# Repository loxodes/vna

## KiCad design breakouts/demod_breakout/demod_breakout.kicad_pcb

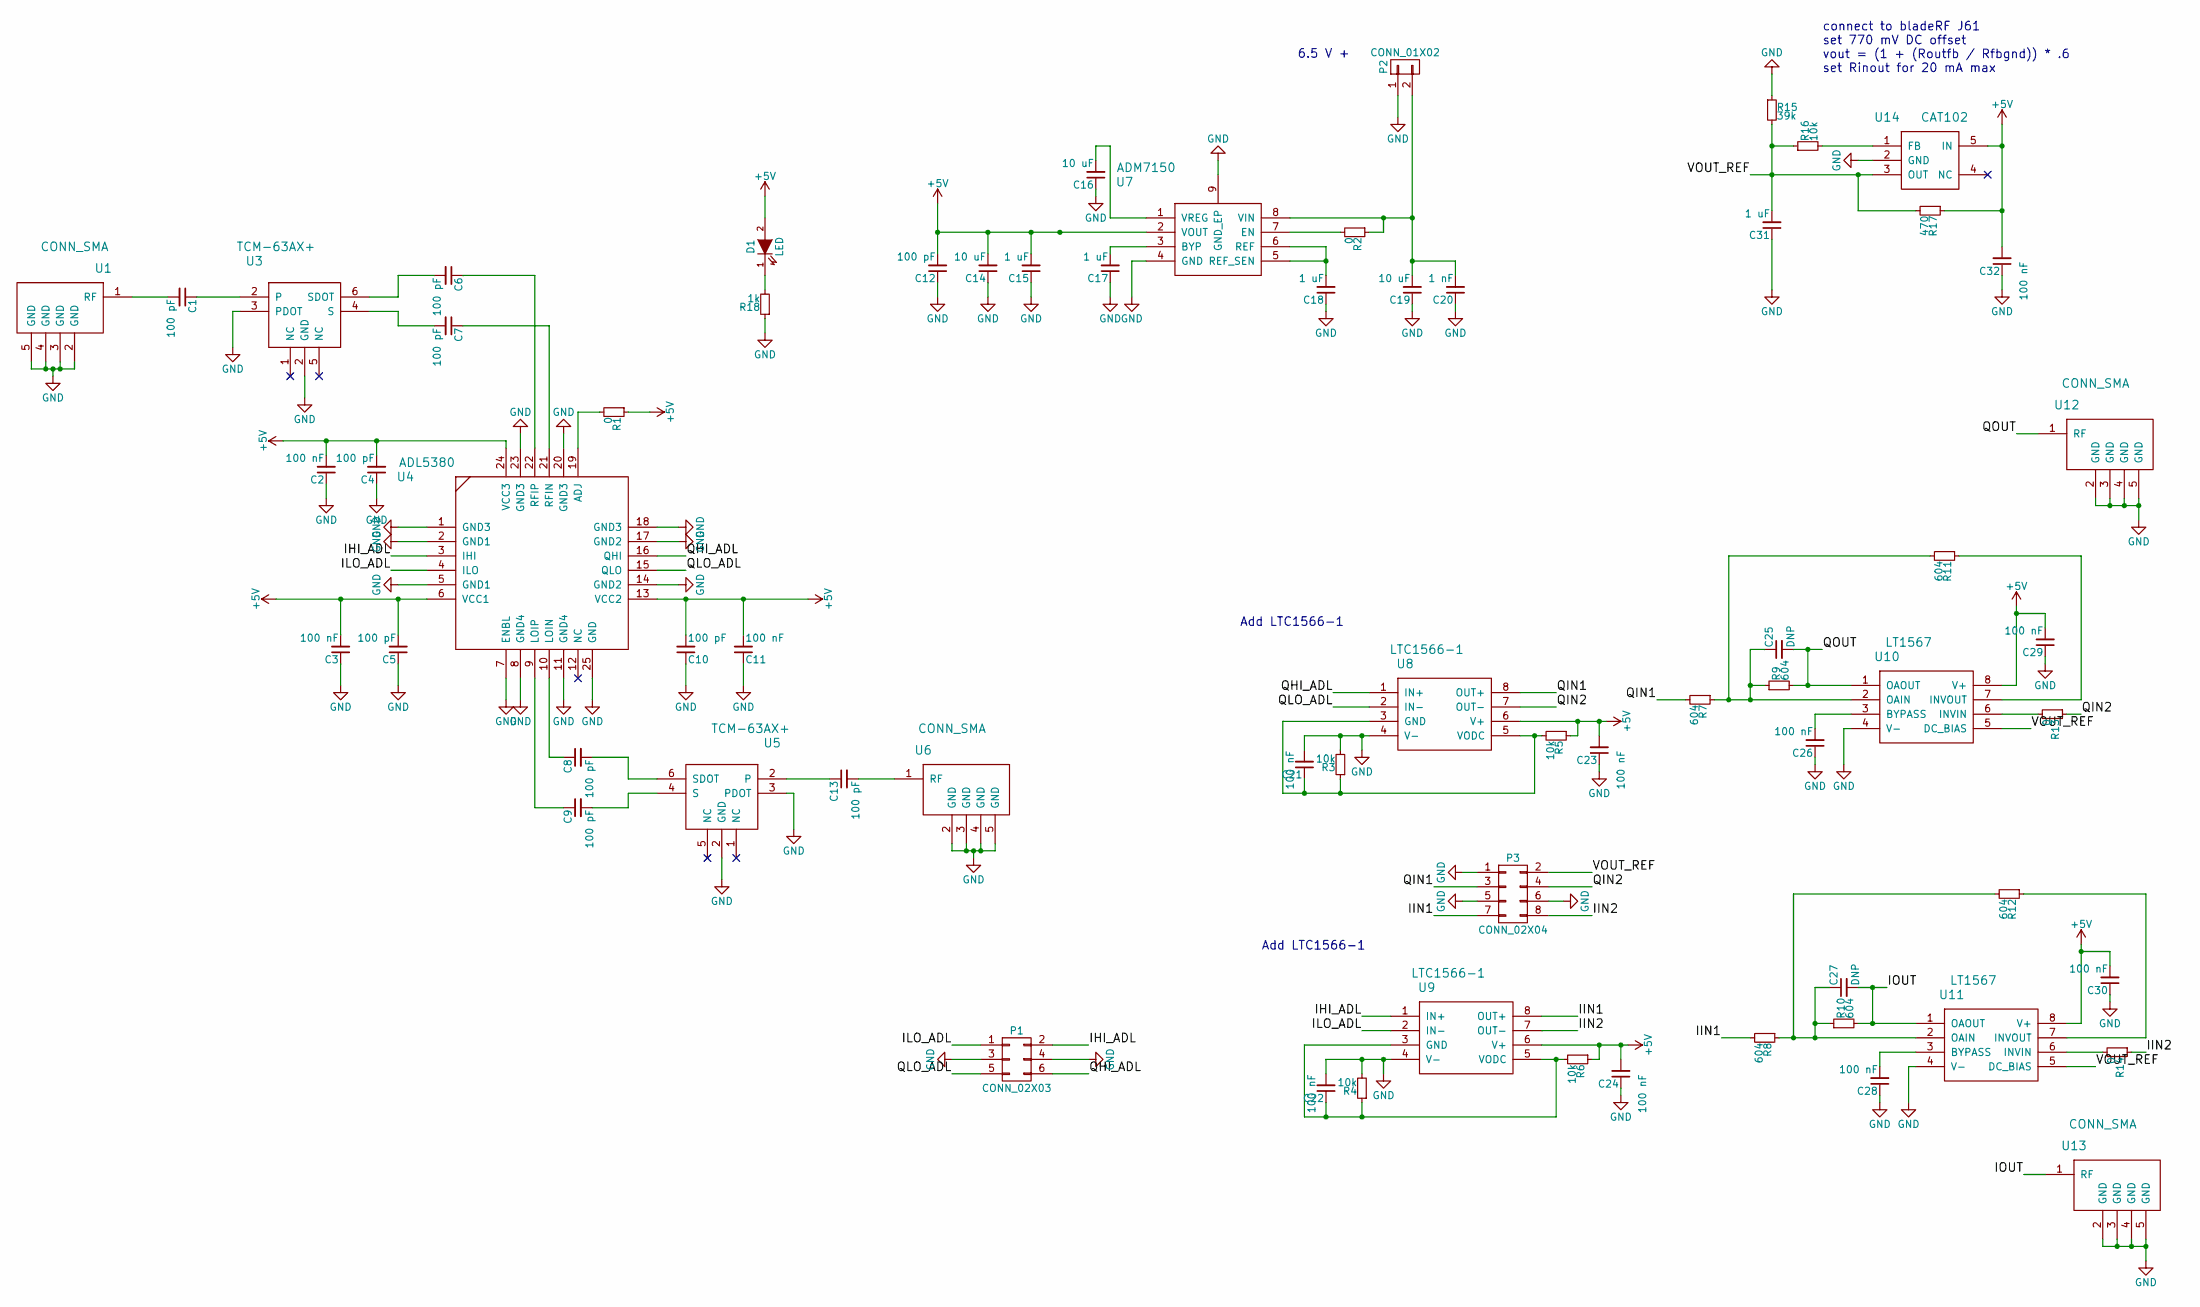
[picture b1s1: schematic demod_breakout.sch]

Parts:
C1, C4, C5, C6, C7, C8, C9, C10, C12, C13: 100 pF; C_0402
C2, C3, C11, C21, C22, C23, C24, C26, C28, C29, C30, C32: 100 nF; C_0402
C14, C16, C19: 10 uF; C_0805
C15, C17, C18, C31: 1 uF; C_0402
C20: 1 nF; C_0402
C25, C27: DNP; C_0402
D1: LED; LED_0603
P1: CONN_02X03; Pin_Header_Straight_2x03
P2: CONN_01X02; Pin_Header_Straight_1x02
P3: CONN_02X04; Pin_Header_Straight_2x04
R1, R2, R13, R14: 0; R_0402
R3, R4, R5, R6, R16: 10k; R_0402
R7, R8, R9, R10, R11, R12: 604; R_0402
R15: 39k; R_0402
R17: 470; R_0402
R18: 1k; R_0402
U1, U6, U12, U13: CONN_SMA; 732512200_SMA
U3, U5: TCM-63AX+; TCM1-63AX+
U4: ADL5380; QFN-24-1EP_4x4mm_Pitch0.5mm
U7: ADM7150; DFN-8-1EP_3x3mm_Pitch0.5mm
U8, U9: LTC1566-1; SOIC-8_3.9x4.9mm_Pitch1.27mm
U10, U11: LT1567; MSOP-8_3x3mm_Pitch0.65mm
U14: CAT102; SOT-23-5

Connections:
+5V: C2.2, C3.2, C4.2, C5.2, C10.2, C11.2, C12.2, C14.2, C15.2, C23.2, C24.2, C29.2, C30.2, C32.2, D1.2 (A), R1.1, R5.1, R6.1, R17.1, U4.6 (VCC1), U4.13 (VCC2), U4.24 (VCC3), U7.2 (VOUT), U8.6 (V+), U9.6 (V+), U10.8 (V+), U11.8 (V+), U14.5 (IN)
/IHI_ADL: P1.2, U4.3 (IHI), U9.1 (IN+)
/IIN1: P3.7, R8.2, U9.8 (OUT+)
/IIN2: P3.8, R14.1, U9.7 (OUT-)
/ILO_ADL: P1.1, U4.4 (ILO), U9.2 (IN-)
/IOUT: C27.2, R10.2, U11.1 (OAOUT), U13.1 (RF)
/QHI_ADL: P1.6, U4.16 (QHI), U8.1 (IN+)
/QIN1: P3.3, R7.2, U8.8 (OUT+)
/QIN2: P3.4, R13.1, U8.7 (OUT-)
/QLO_ADL: P1.5, U4.15 (QLO), U8.2 (IN-)
/QOUT: C25.2, R9.2, U10.1 (OAOUT), U12.1 (RF)
/VOUT_REF: C31.2, P3.2, R15.2, R16.1, R17.2, U10.5 (DC_BIAS), U11.5 (DC_BIAS), U14.3 (OUT)
unnamed: C1.2, U1.1 (RF)
unnamed: C6.1, U4.22 (RFIP)
unnamed: C6.2, U3.6 (SDOT)
unnamed: C7.1, U4.21 (RFIN)
unnamed: C7.2, U3.4 (S)
unnamed: C8.1, U4.10 (LOIN)
unnamed: C8.2, U5.6 (SDOT)
unnamed: C9.1, U4.9 (LOIP)
unnamed: C9.2, U5.4 (S)
unnamed: C13.2, U6.1 (RF)
unnamed: C16.2, U7.1 (VREG)
unnamed: C17.2, U7.3 (BYP)
unnamed: C18.2, U7.5 (REF_SEN), U7.6 (REF)
unnamed: C19.2, C20.2, P2.2, R2.1, U7.8 (VIN)
unnamed: C21.1, R3.1, R5.2, U8.3 (GND), U8.5 (VODC)
unnamed: C22.1, R4.1, R6.2, U9.3 (GND), U9.5 (VODC)
unnamed: C25.1, R7.1, R9.1, R11.2, U10.2 (OAIN)
unnamed: C26.2, U10.3 (BYPASS)
unnamed: C27.1, R8.1, R10.1, R12.2, U11.2 (OAIN)
unnamed: C28.2, U11.3 (BYPASS)
unnamed: D1.1 (K), R18.2
unnamed: R1.2, U4.19 (ADJ)
unnamed: R2.2, U7.7 (EN)
unnamed: R11.1, U10.7 (INVOUT)
unnamed: R12.1, U11.7 (INVOUT)
unnamed: R13.2, U10.6 (INVIN)
unnamed: R14.2, U11.6 (INVIN)
unnamed: R16.2, U14.1 (FB)

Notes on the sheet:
6.5 V +
connect to bladeRF J61 set 770 mV DC offset vout = (1 + (Routfb / Rfbgnd)) * .6 set Rinout for 20 mA max
Add LTC1566-1

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
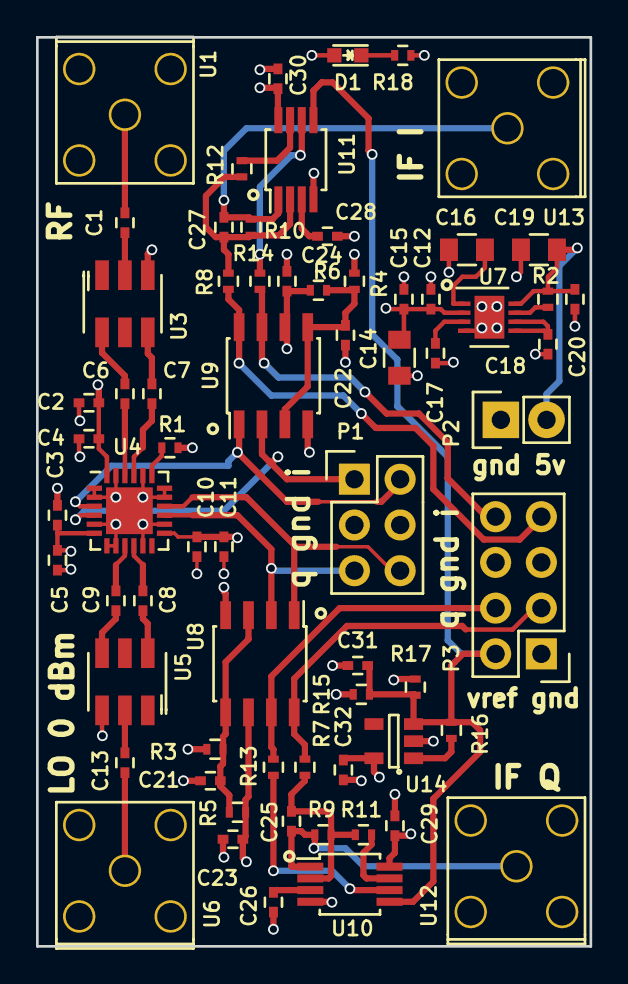
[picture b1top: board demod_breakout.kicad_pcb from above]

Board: 4 copper layers, 30.8 x 50.5 mm, 67 parts (0 on the bottom side), 43 nets.

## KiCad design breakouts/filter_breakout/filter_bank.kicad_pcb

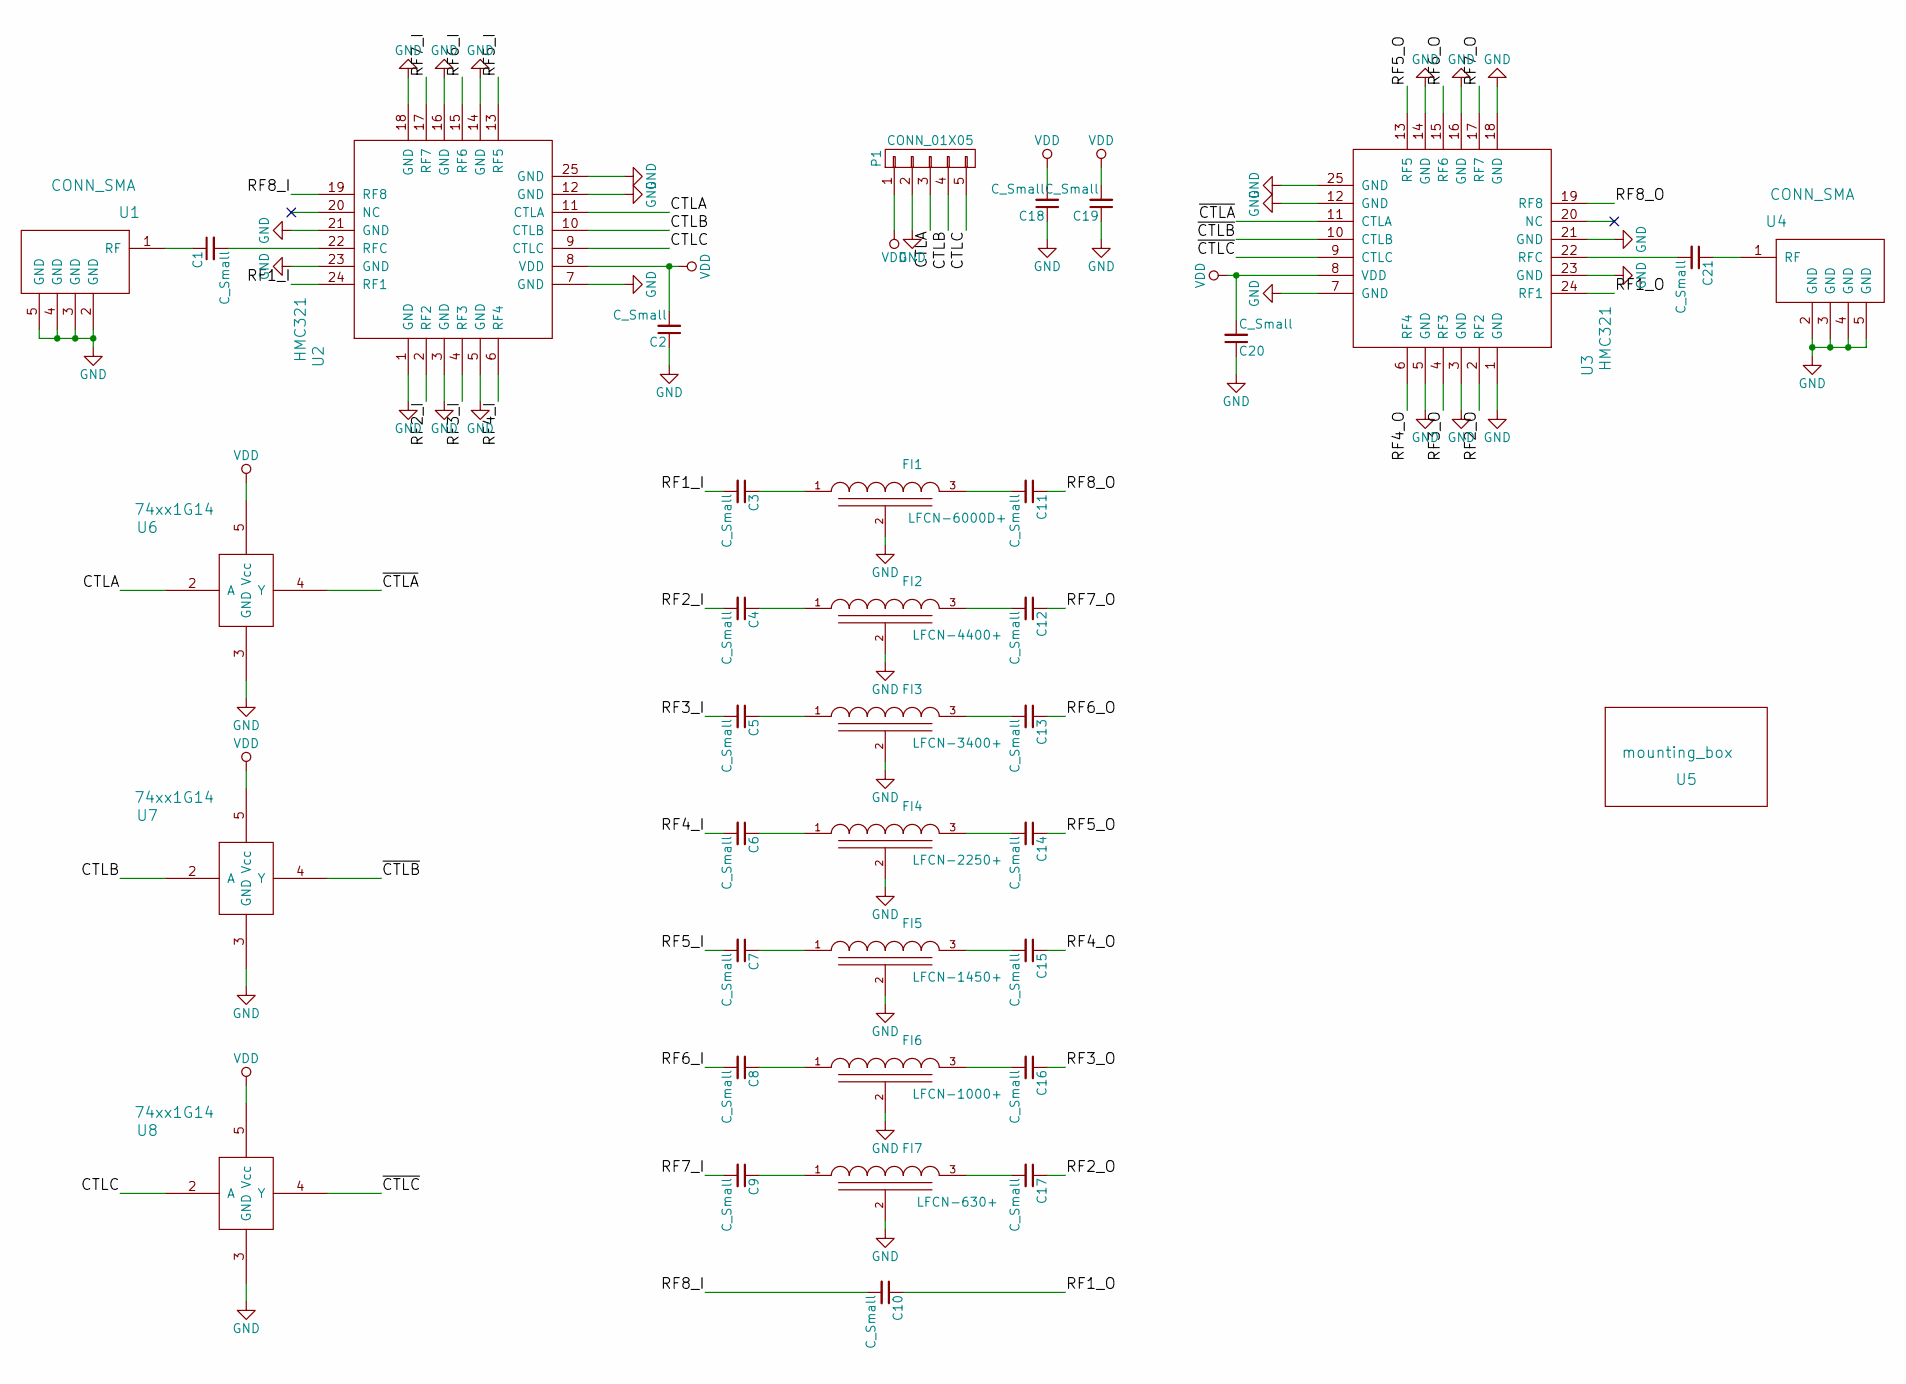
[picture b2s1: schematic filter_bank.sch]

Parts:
C1, C2, C3, C4, C5, C6, C7, C8, C9, C10, C11, C12, C13, C14, C15, C16, C17, C19, C20, C21: C_Small; C_0402
C18: C_Small; C_0805
FI1: LFCN-6000D+; FV1206
FI2: LFCN-4400+; FV1206
FI3: LFCN-3400+; FV1206
FI4: LFCN-2250+; FV1206
FI5: LFCN-1450+; FV1206
FI6: LFCN-1000+; FV1206
FI7: LFCN-630+; FV1206
P1: CONN_01X05; Pin_Header_Straight_1x05
U1, U4: CONN_SMA; 732511150_sma
U2, U3: HMC321; QFN-24-1EP_4x4mm_Pitch0.5mm
U5: mounting_box; POMONA_2400BOX
U6, U7, U8: 74xx1G14; SOT-23-5

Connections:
/CTLA: P1.3, U2.11 (CTLA), U6.2 (A)
/CTLB: P1.4, U2.10 (CTLB), U7.2 (A)
/CTLC: P1.5, U2.9 (CTLC), U8.2 (A)
/RF1_I: C3.2, U2.24 (RF1)
/RF1_O: C10.1, U3.24 (RF1)
/RF2_I: C4.2, U2.2 (RF2)
/RF2_O: C17.1, U3.2 (RF2)
/RF3_I: C5.2, U2.4 (RF3)
/RF3_O: C16.1, U3.4 (RF3)
/RF4_I: C6.2, U2.6 (RF4)
/RF4_O: C15.1, U3.6 (RF4)
/RF5_I: C7.2, U2.13 (RF5)
/RF5_O: C14.1, U3.13 (RF5)
/RF6_I: C8.2, U2.15 (RF6)
/RF6_O: C13.1, U3.15 (RF6)
/RF7_I: C9.2, U2.17 (RF7)
/RF7_O: C12.1, U3.17 (RF7)
/RF8_I: C10.2, U2.19 (RF8)
/RF8_O: C11.1, U3.19 (RF8)
/~CTLA: U3.11 (CTLA), U6.4 (Y)
/~CTLB: U3.10 (CTLB), U7.4 (Y)
/~CTLC: U3.9 (CTLC), U8.4 (Y)
GND: C2.1, C18.1, C19.1, C20.1, FI1.2 (GND), FI2.2 (GND), FI3.2 (GND), FI4.2 (GND), FI5.2 (GND), FI6.2 (GND), FI7.2 (GND), P1.2, U1.2 (GND), U1.3 (GND), U1.4 (GND), U1.5 (GND), U2.1 (GND), U2.3 (GND), U2.5 (GND), U2.7 (GND), U2.12 (GND), U2.14 (GND), U2.16 (GND), U2.18 (GND), U2.21 (GND), U2.23 (GND), U2.25 (GND), U3.1 (GND), U3.3 (GND), U3.5 (GND), U3.7 (GND), U3.12 (GND), U3.14 (GND), U3.16 (GND), U3.18 (GND), U3.21 (GND), U3.23 (GND), U3.25 (GND), U4.2 (GND), U4.3 (GND), U4.4 (GND), U4.5 (GND), U6.3 (GND), U7.3 (GND), U8.3 (GND)
unnamed: C1.1, U1.1 (RF)
unnamed: C1.2, U2.22 (RFC)
unnamed: C3.1, FI1.1 (VI)
unnamed: C4.1, FI2.1 (VI)
unnamed: C5.1, FI3.1 (VI)
unnamed: C6.1, FI4.1 (VI)
unnamed: C7.1, FI5.1 (VI)
unnamed: C8.1, FI6.1 (VI)
unnamed: C9.1, FI7.1 (VI)
unnamed: C11.2, FI1.3 (VO)
unnamed: C12.2, FI2.3 (VO)
unnamed: C13.2, FI3.3 (VO)
unnamed: C14.2, FI4.3 (VO)
unnamed: C15.2, FI5.3 (VO)
unnamed: C16.2, FI6.3 (VO)
unnamed: C17.2, FI7.3 (VO)
unnamed: C21.1, U4.1 (RF)
unnamed: C21.2, U3.22 (RFC)
VDD: C2.2, C18.2, C19.2, C20.2, P1.1, U2.8 (VDD), U3.8 (VDD), U6.5 (Vcc), U7.5 (Vcc), U8.5 (Vcc)

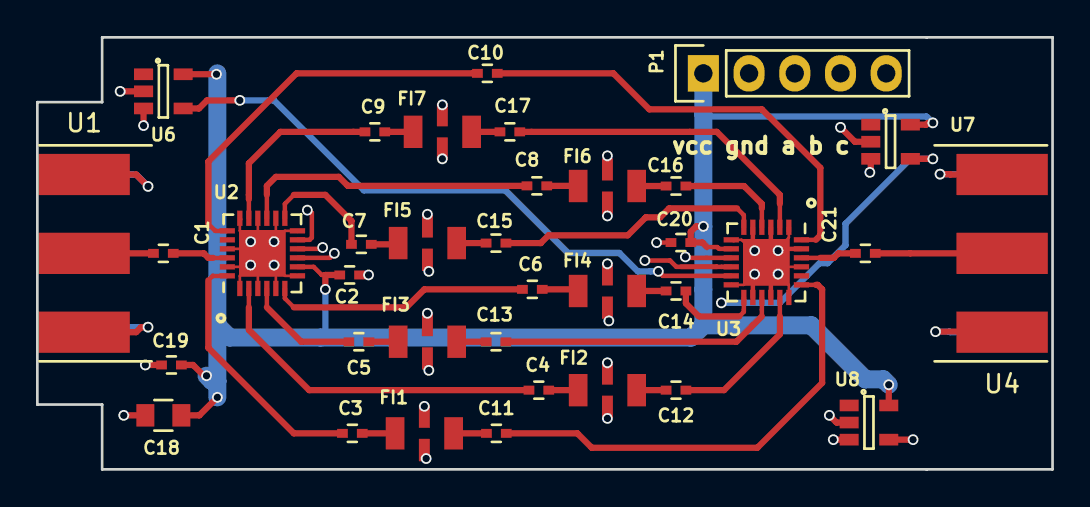
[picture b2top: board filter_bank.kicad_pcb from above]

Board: 4 copper layers, 56.4 x 24.0 mm, 36 parts (0 on the bottom side), 42 nets.

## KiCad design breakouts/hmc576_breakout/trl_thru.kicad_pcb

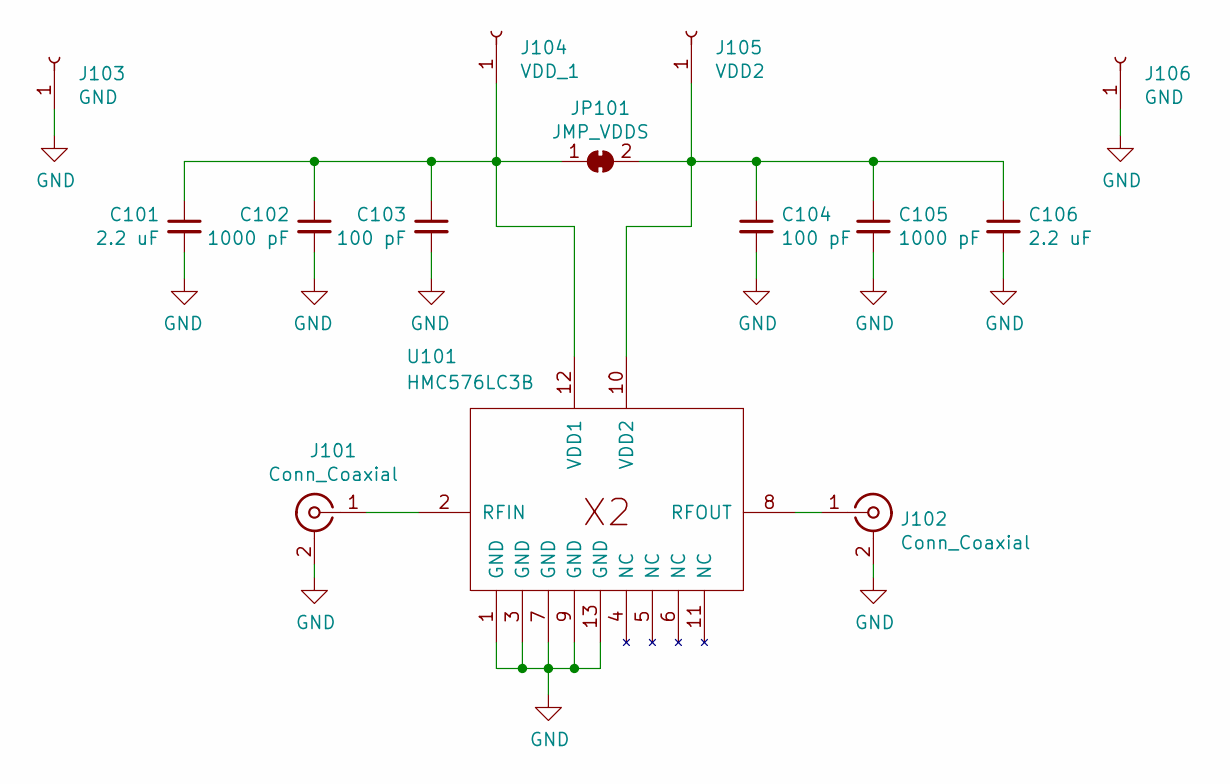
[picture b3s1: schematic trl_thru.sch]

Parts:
C101, C106: 2.2 uF; C_0805
C102, C105: 1000 pF; C_0402
C103, C104: 100 pF; C_0402
J101, J102: Conn_Coaxial; sw_edge_oshpark_4layer
J103, J106: GND; TURRET_MILLMAX_2101
J104: VDD_1; TURRET_MILLMAX_2101
J105: VDD2; TURRET_MILLMAX_2101
JP101: JMP_VDDS; R_0402
U101: HMC576LC3B; LC3B

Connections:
GND: C101.2, C102.2, C103.2, C104.2, C105.2, C106.2, J101.2 (Ext), J102.2 (Ext), J103.1, J106.1, U101.1 (GND), U101.3 (GND), U101.7 (GND), U101.9 (GND), U101.13 (GND)
unnamed: C101.1, C102.1, C103.1, J104.1, JP101.1 (A), U101.12 (VDD1)
unnamed: C104.1, C105.1, C106.1, J105.1, JP101.2 (B), U101.10 (VDD2)
unnamed: J101.1 (In), U101.2 (RFIN)
unnamed: J102.1 (In), U101.8 (RFOUT)

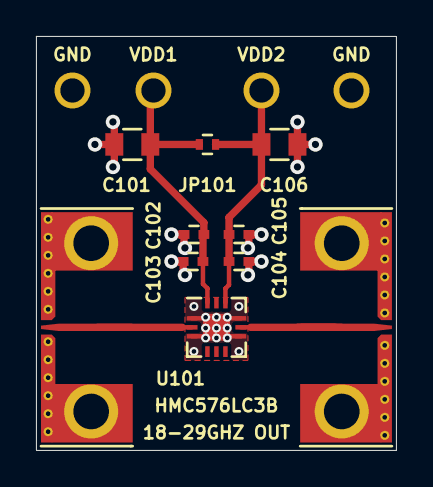
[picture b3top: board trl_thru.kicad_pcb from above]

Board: 4 copper layers, 20.0 x 23.0 mm, 14 parts (0 on the bottom side), 5 nets.

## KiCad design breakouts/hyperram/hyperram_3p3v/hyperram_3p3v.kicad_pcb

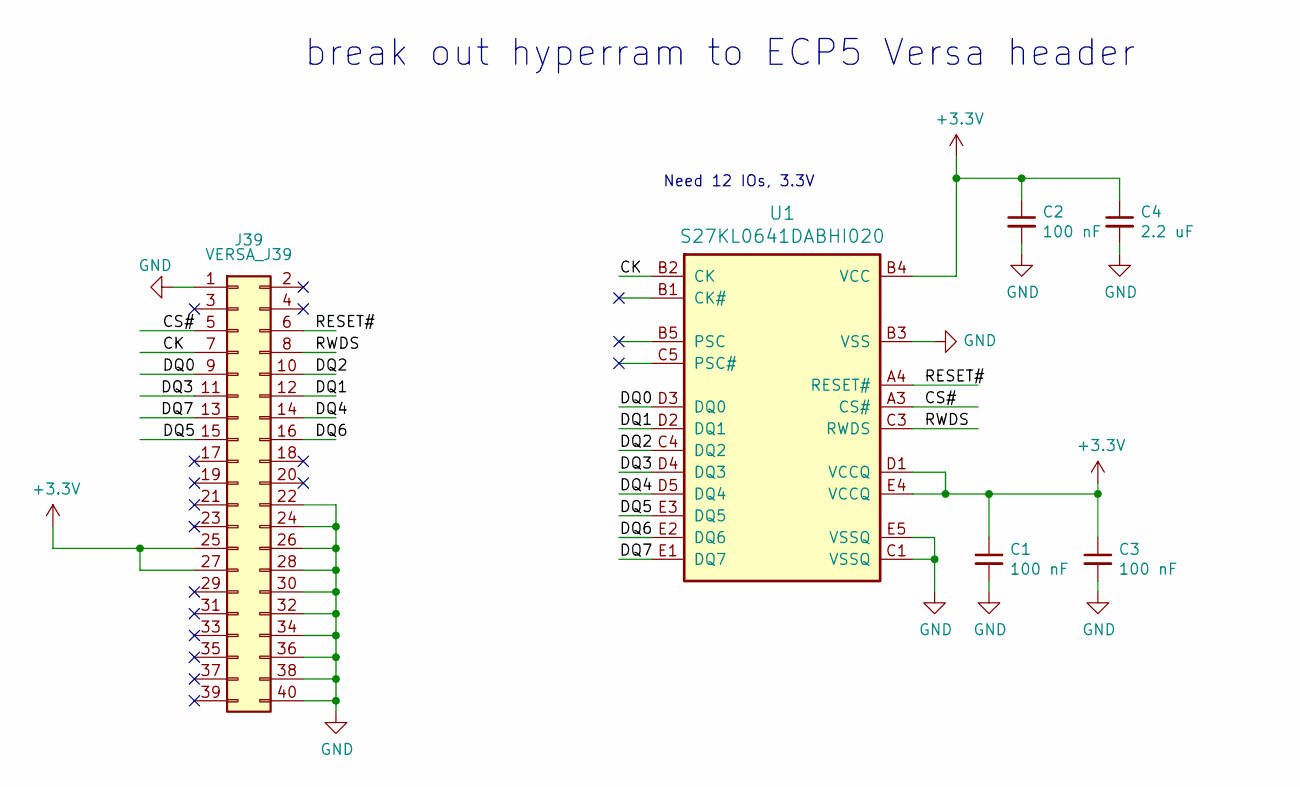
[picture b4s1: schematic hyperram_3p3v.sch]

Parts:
C1, C2, C3: 100 nF; C_0402_1005Metric
C4: 2.2 uF; C_0603_1608Metric
J39: VERSA_J39; PinSocket_2x20_P2.54mm_Vertical
U1: S27KL0641DABHI020; T-PBGA-24_6.0x8.0mm_Layout5x5_P1.0mm

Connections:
+3V3: C1.1, C2.1, C3.1, C4.1, J39.25, J39.27, U1.B4 (VCC), U1.D1 (VCCQ), U1.E4 (VCCQ)
/CK: J39.7, U1.B2 (CK)
/CS#: J39.5, U1.A3 (CS#)
/DQ0: J39.9, U1.D3 (DQ0)
/DQ1: J39.12, U1.D2 (DQ1)
/DQ2: J39.10, U1.C4 (DQ2)
/DQ3: J39.11, U1.D4 (DQ3)
/DQ4: J39.14, U1.D5 (DQ4)
/DQ5: J39.15, U1.E3 (DQ5)
/DQ6: J39.16, U1.E2 (DQ6)
/DQ7: J39.13, U1.E1 (DQ7)
/RESET#: J39.6, U1.A4 (RESET#)
/RWDS: J39.8, U1.C3 (RWDS)
GND: C1.2, C2.2, C3.2, C4.2, J39.1, J39.22, J39.24, J39.26, J39.28, J39.30, J39.32, J39.34, J39.36, J39.38, J39.40, U1.B3 (VSS), U1.C1 (VSSQ), U1.E5 (VSSQ)

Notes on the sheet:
Need 12 IOs, 3.3V
break out hyperram to ECP5 Versa header

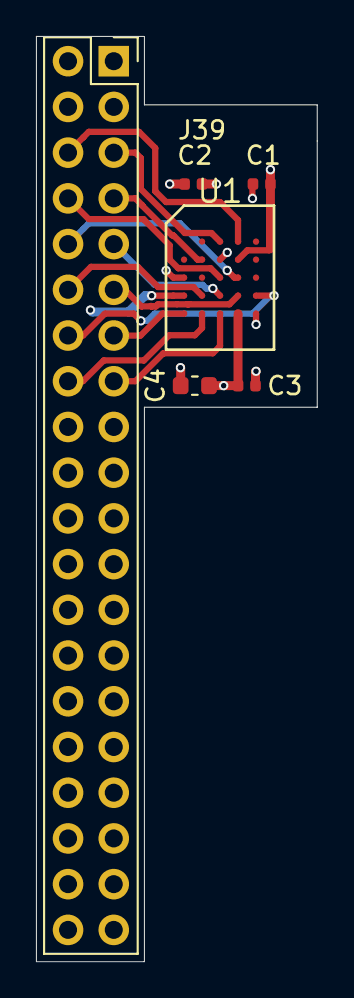
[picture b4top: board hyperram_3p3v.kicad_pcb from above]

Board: 4 copper layers, 15.6 x 51.4 mm, 6 parts (0 on the bottom side), 14 nets.

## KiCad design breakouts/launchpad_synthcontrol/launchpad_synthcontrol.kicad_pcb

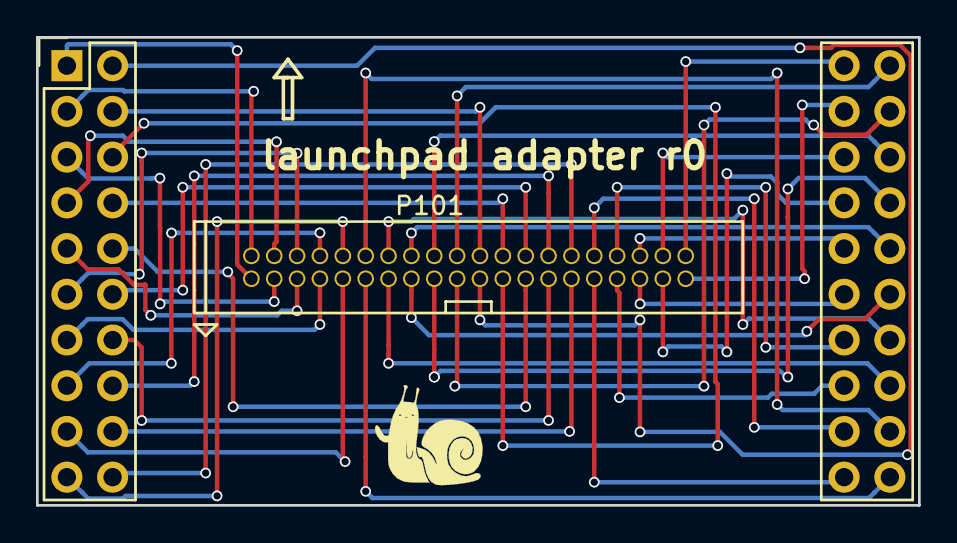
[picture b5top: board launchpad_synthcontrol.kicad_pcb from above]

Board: 2 copper layers, 49.0 x 26.0 mm, 3 parts (0 on the bottom side), 40 nets.

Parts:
P101: CONN_01X40; 3221-40-0100-00_conn40
P102: CONN_01X40; ti_booster40
U101: snail

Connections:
unnamed: P101.1, P102.1
unnamed: P101.2, P102.2
unnamed: P101.3, P102.3
unnamed: P101.4, P102.4
unnamed: P101.5, P102.5
unnamed: P101.6, P102.6
unnamed: P101.7, P102.7
unnamed: P101.8, P102.8
unnamed: P101.9, P102.9
unnamed: P101.10, P102.10
unnamed: P101.11, P102.11
unnamed: P101.12, P102.12
unnamed: P101.13, P102.13
unnamed: P101.14, P102.14
unnamed: P101.15, P102.15
unnamed: P101.16, P102.16
unnamed: P101.17, P102.17
unnamed: P101.18, P102.18
unnamed: P101.19, P102.19
unnamed: P101.20, P102.20
unnamed: P101.21, P102.21
unnamed: P101.22, P102.22
unnamed: P101.23, P102.23
unnamed: P101.24, P102.24
unnamed: P101.25, P102.25
unnamed: P101.26, P102.26
unnamed: P101.27, P102.27
unnamed: P101.28, P102.28
unnamed: P101.29, P102.29
unnamed: P101.30, P102.30
unnamed: P101.31, P102.31
unnamed: P101.32, P102.32
unnamed: P101.33, P102.33
unnamed: P101.34, P102.34
unnamed: P101.35, P102.35
unnamed: P101.36, P102.36
unnamed: P101.37, P102.37
unnamed: P101.38, P102.38
unnamed: P101.39, P102.39
unnamed: P101.40, P102.40

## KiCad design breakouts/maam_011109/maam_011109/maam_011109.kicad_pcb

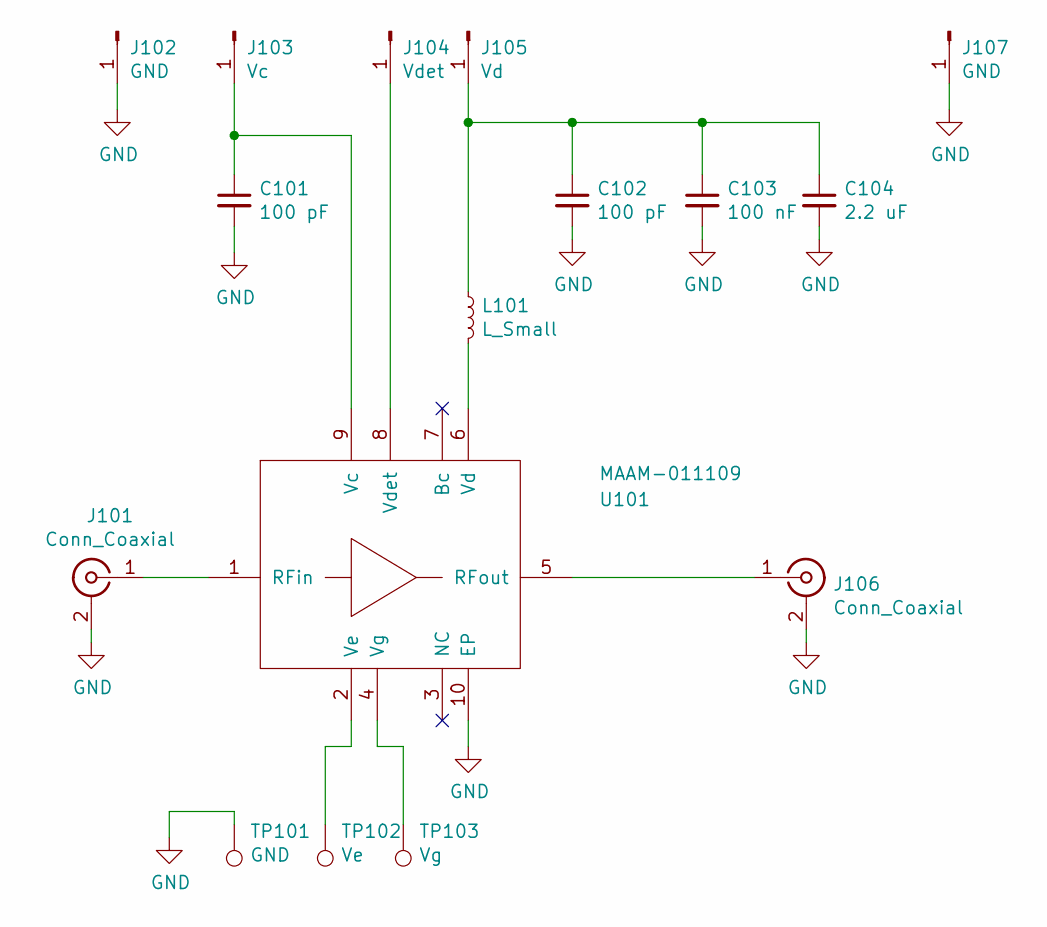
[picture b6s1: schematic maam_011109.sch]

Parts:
C101, C102: 100 pF; C_0402
C103: 100 nF; C_0402
C104: 2.2 uF; C_0603
J101, J106: Conn_Coaxial; sw_edge_oshpark_4layer
J102, J107: GND; TURRET_MILLMAX_2101
J103: Vc; TURRET_MILLMAX_2101
J104: Vdet; TURRET_MILLMAX_2101
J105: Vd; TURRET_MILLMAX_2101
L101: L_Small; C_0402
TP101: GND; TP07R
TP102: Ve; TP07R
TP103: Vg; TP07R
U101: MAAM-011109; MACOM_LGA9

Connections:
GND: C101.2, C102.2, C103.2, C104.2, J101.2 (Ext), J102.1, J106.2 (Ext), J107.1, TP101.1, U101.10 (EP)
unnamed: C101.1, J103.1, U101.9 (Vc)
unnamed: C102.1, C103.1, C104.1, J105.1, L101.1
unnamed: J101.1 (In), U101.1 (RFin)
unnamed: J104.1, U101.8 (Vdet)
unnamed: J106.1 (In), U101.5 (RFout)
unnamed: L101.2, U101.6 (Vd)
unnamed: TP102.1, U101.2 (Ve)
unnamed: TP103.1, U101.4 (Vg)

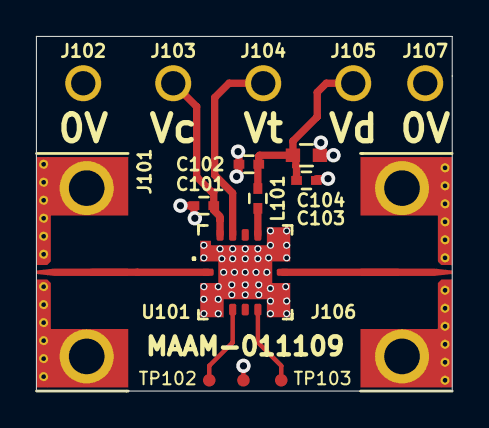
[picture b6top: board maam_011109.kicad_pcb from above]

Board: 4 copper layers, 23.1 x 19.7 mm, 16 parts (0 on the bottom side), 9 nets.

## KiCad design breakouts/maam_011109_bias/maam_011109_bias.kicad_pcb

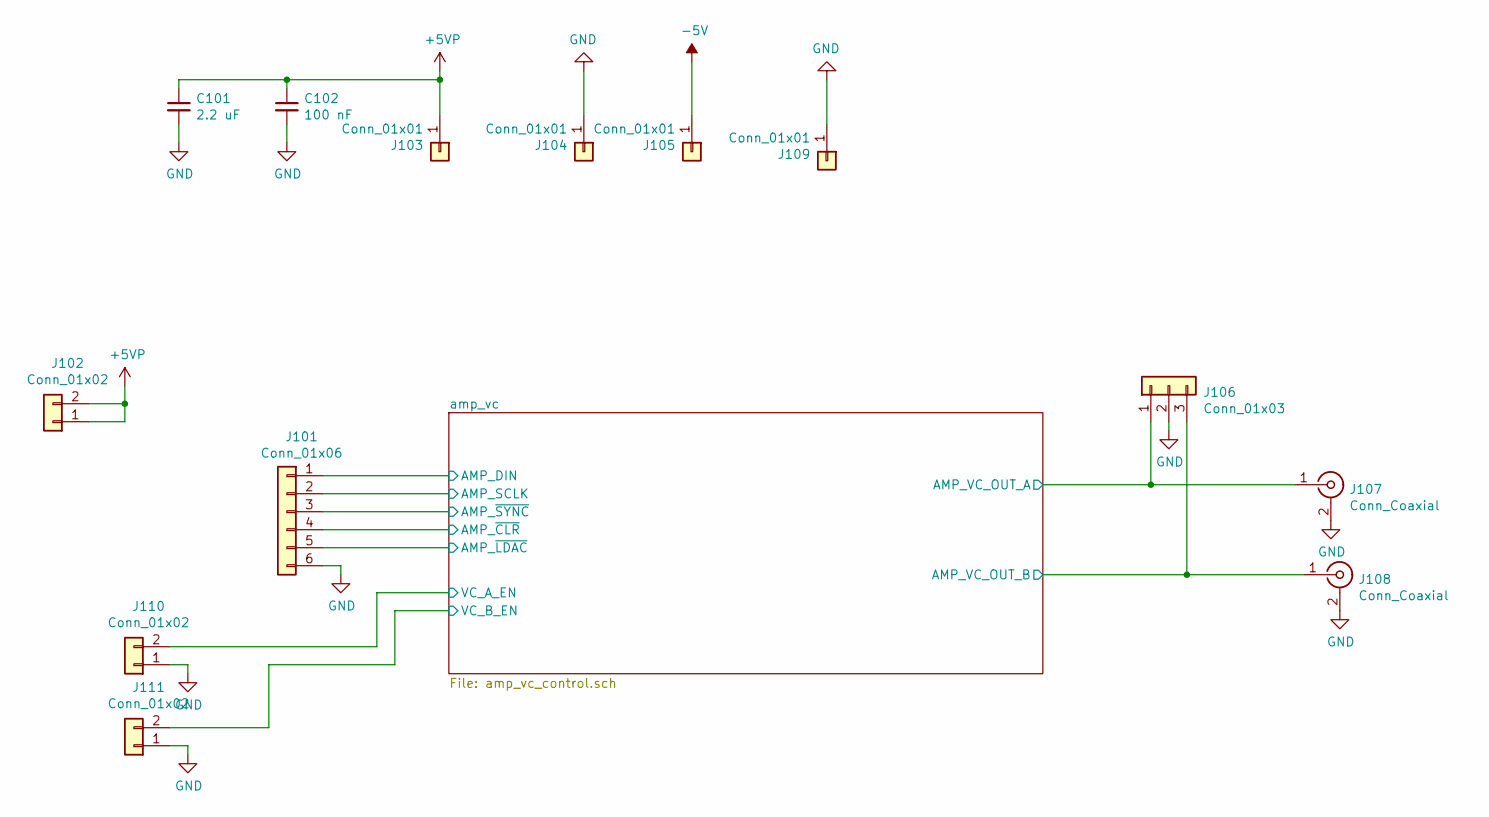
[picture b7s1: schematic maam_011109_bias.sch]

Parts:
C101: 2.2 uF; C_0603
C102: 100 nF; C_0402
J101: Conn_01x06; Pin_Header_Straight_1x06
J102, J110, J111: Conn_01x02; Pin_Header_Straight_1x02
J103, J104, J105, J109: Conn_01x01; TURRET_MILLMAX_2101
J106: Conn_01x03; Pin_Header_Straight_1x03
J107, J108: Conn_Coaxial; 732512200_SMA

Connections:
+5VP: C101.1, C102.1, J102.1, J102.2, J103.1; also elsewhere on the board
-5V: J105.1; also elsewhere on the board
/amp_vc/AMP_DIN: J101.1; also elsewhere on the board
/amp_vc/AMP_SCLK: J101.2; also elsewhere on the board
/amp_vc/AMP_VC_OUT_A: J106.1, J107.1 (In); also elsewhere on the board
/amp_vc/AMP_VC_OUT_B: J106.3, J108.1 (In); also elsewhere on the board
/amp_vc/AMP_~CLR: J101.4; also elsewhere on the board
/amp_vc/AMP_~LDAC: J101.5; also elsewhere on the board
/amp_vc/AMP_~SYNC: J101.3; also elsewhere on the board
/amp_vc/VC_A_EN: J110.2; also elsewhere on the board
/amp_vc/VC_B_EN: J111.2; also elsewhere on the board
GND: C101.2, C102.2, J101.6, J104.1, J106.2, J107.2 (Ext), J108.2 (Ext), J109.1, J110.1, J111.1; also elsewhere on the board

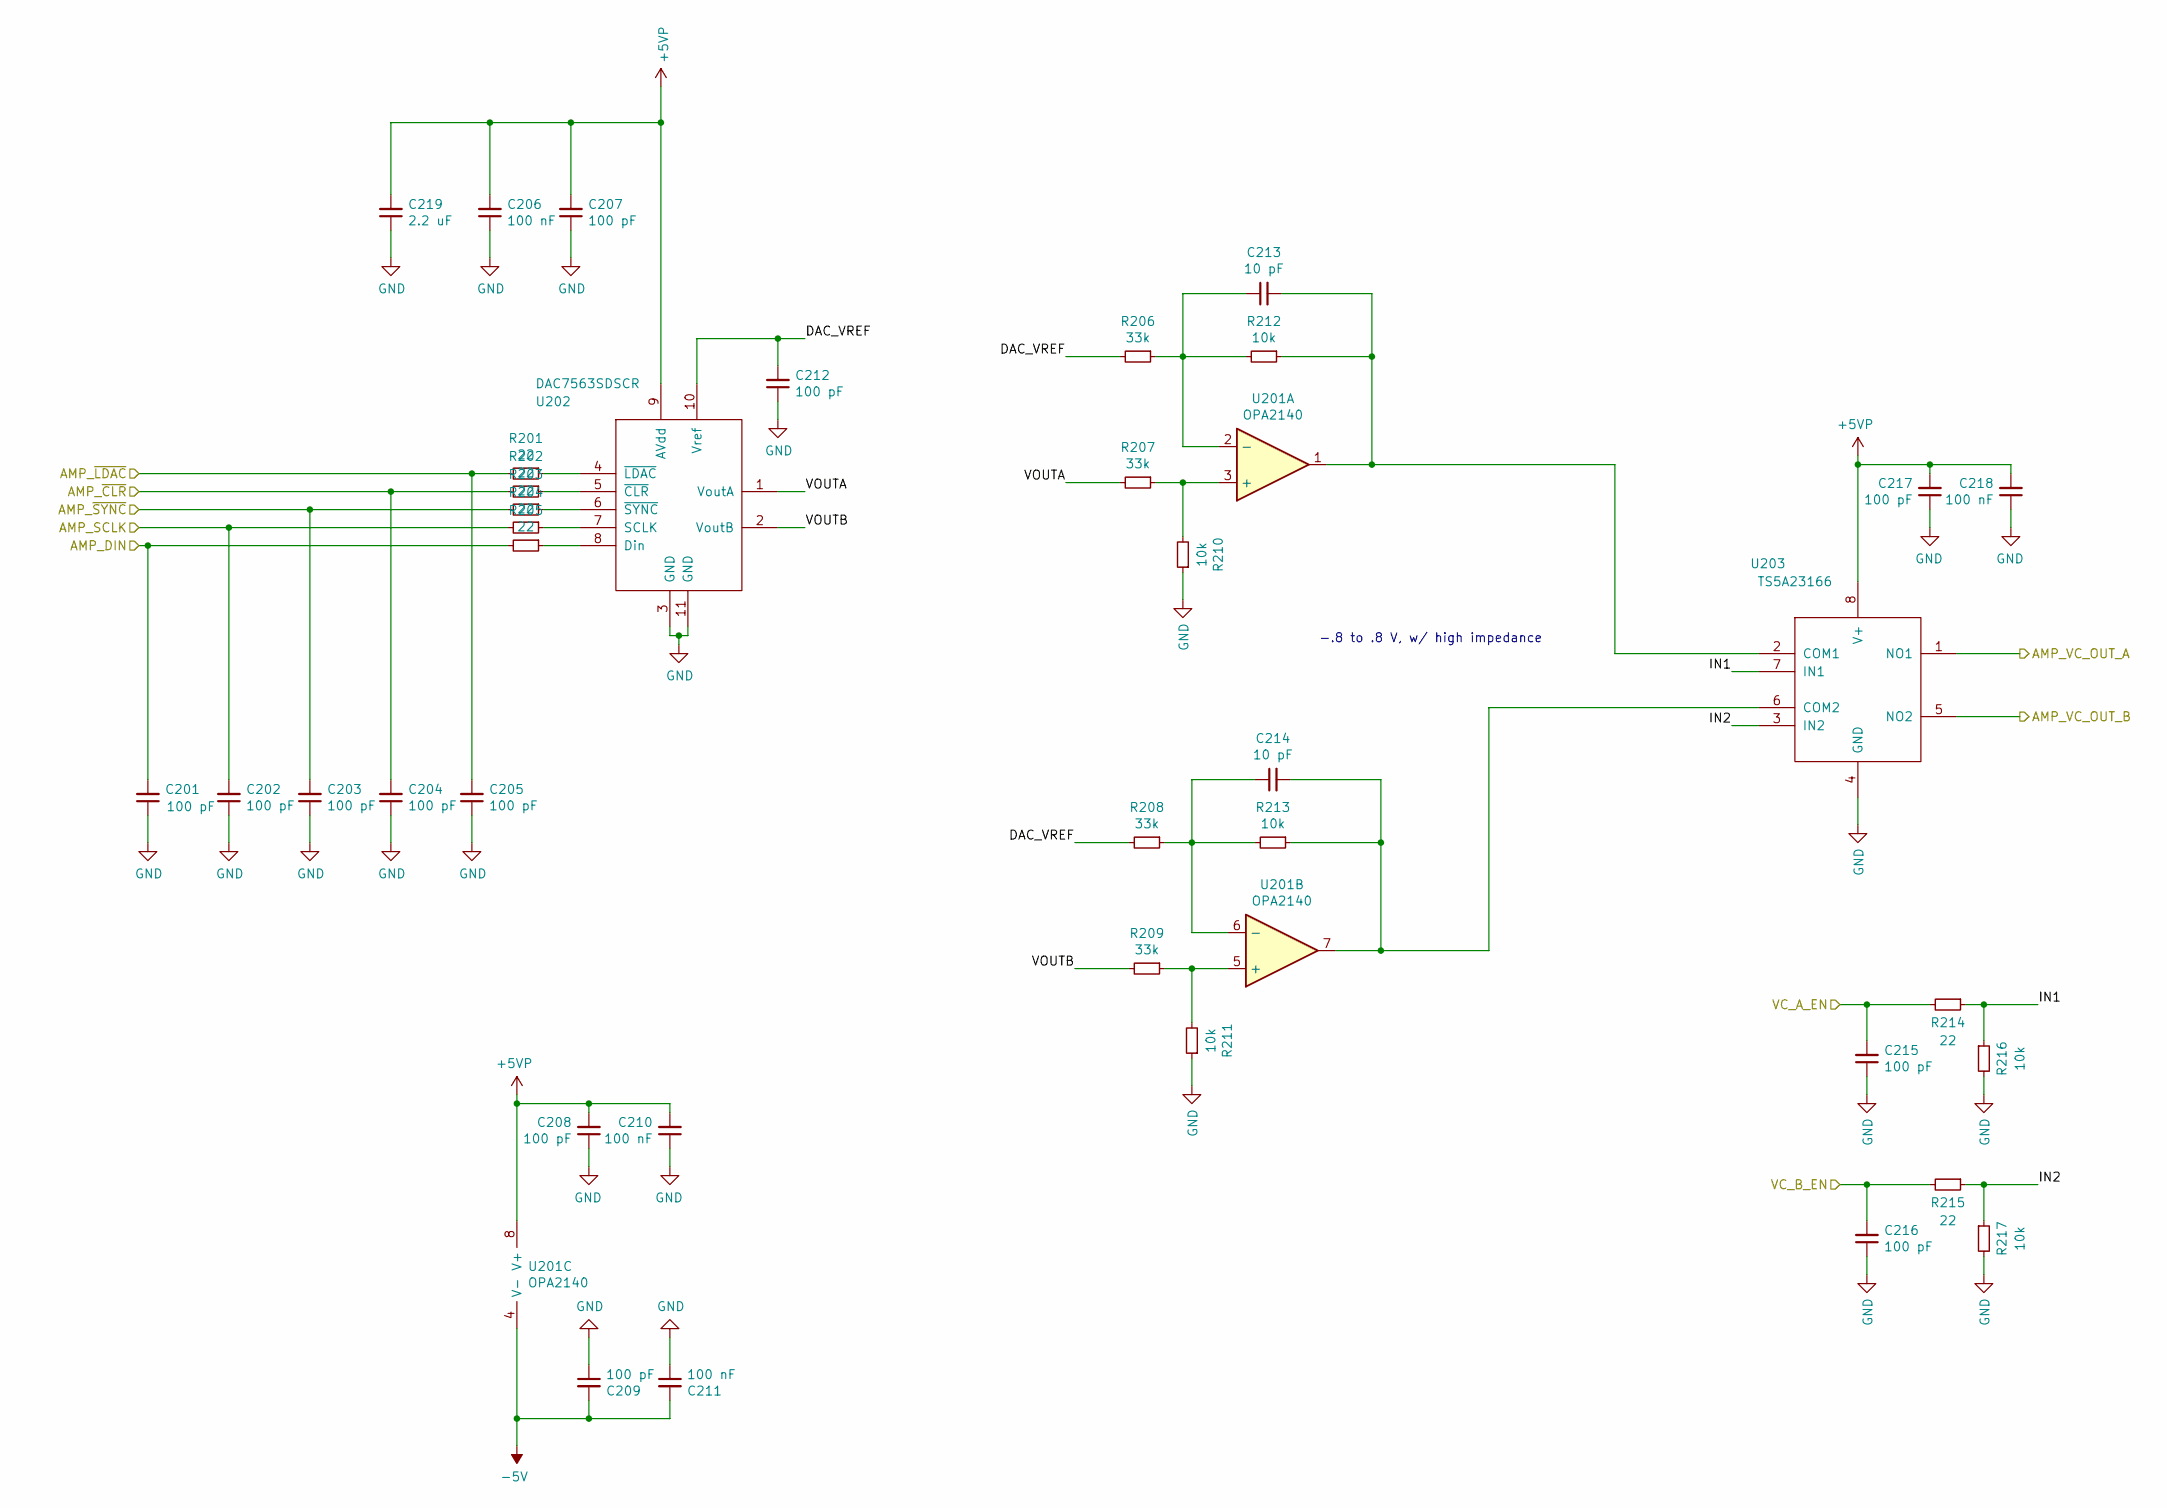
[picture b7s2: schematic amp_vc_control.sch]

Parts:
C201, C202, C203, C204, C205, C207, C208, C209, C212, C215, C216, C217: 100 pF; C_0402
C206, C210, C211, C218: 100 nF; C_0402
C213, C214: 10 pF; C_0402
C219: 2.2 uF; C_0603
R201, R202, R203, R204, R205, R214, R215: 22; R_0402
R206, R207, R208, R209: 33k; R_0603
R210, R211, R212, R213: 10k; R_0603
R216, R217: 10k; R_0402
U201: OPA2140; MSOP-8_3x3mm_Pitch0.65mm
U202: DAC7563SDSCR; DFN-10-1EP_3x3mm_Pitch0.5mm
U203: TS5A23166; VSSOP-8

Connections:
+5VP: C206.2, C207.2, C208.2, C210.2, C217.2, C218.2, C219.2, U201.8 (V+), U202.9 (AVdd), U203.8 (V+); also elsewhere on the board
-5V: C209.2, C211.2, U201.4 (V-); also elsewhere on the board
/amp_vc/AMP_DIN: C201.2, R205.2; also elsewhere on the board
/amp_vc/AMP_SCLK: C202.2, R204.2; also elsewhere on the board
/amp_vc/AMP_VC_OUT_A: U203.1 (NO1); also elsewhere on the board
/amp_vc/AMP_VC_OUT_B: U203.5 (NO2); also elsewhere on the board
/amp_vc/AMP_~CLR: C204.2, R202.2; also elsewhere on the board
/amp_vc/AMP_~LDAC: C205.2, R201.2; also elsewhere on the board
/amp_vc/AMP_~SYNC: C203.2, R203.2; also elsewhere on the board
/amp_vc/DAC_VREF: C212.2, R206.2, R208.2, U202.10 (Vref)
/amp_vc/IN1: R214.1, R216.1, U203.7 (IN1)
/amp_vc/IN2: R215.1, R217.1, U203.3 (IN2)
/amp_vc/VC_A_EN: C215.2, R214.2; also elsewhere on the board
/amp_vc/VC_B_EN: C216.2, R215.2; also elsewhere on the board
/amp_vc/VOUTA: R207.2, U202.1 (VoutA)
/amp_vc/VOUTB: R209.2, U202.2 (VoutB)
GND: C201.1, C202.1, C203.1, C204.1, C205.1, C206.1, C207.1, C208.1, C209.1, C210.1, C211.1, C212.1, C215.1, C216.1, C217.1, C218.1, C219.1, R210.1, R211.1, R216.2, R217.2, U202.3 (GND), U202.11 (GND), U203.4 (GND); also elsewhere on the board
unnamed: C213.1, R206.1, R212.2, U201.2 (-)
unnamed: C213.2, R212.1, U201.1, U203.2 (COM1)
unnamed: C214.1, R208.1, R213.2, U201.6 (-)
unnamed: C214.2, R213.1, U201.7, U203.6 (COM2)
unnamed: R201.1, U202.4 (~LDAC)
unnamed: R202.1, U202.5 (~CLR)
unnamed: R203.1, U202.6 (~SYNC)
unnamed: R204.1, U202.7 (SCLK)
unnamed: R205.1, U202.8 (Din)
unnamed: R207.1, R210.2, U201.3 (+)
unnamed: R209.1, R211.2, U201.5 (+)

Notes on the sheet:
-.8 to .8 V, w/ high impedance
